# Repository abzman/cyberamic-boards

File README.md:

defunct repo, contents moved to https://github.com/palazzol/CyberamicControlCenter

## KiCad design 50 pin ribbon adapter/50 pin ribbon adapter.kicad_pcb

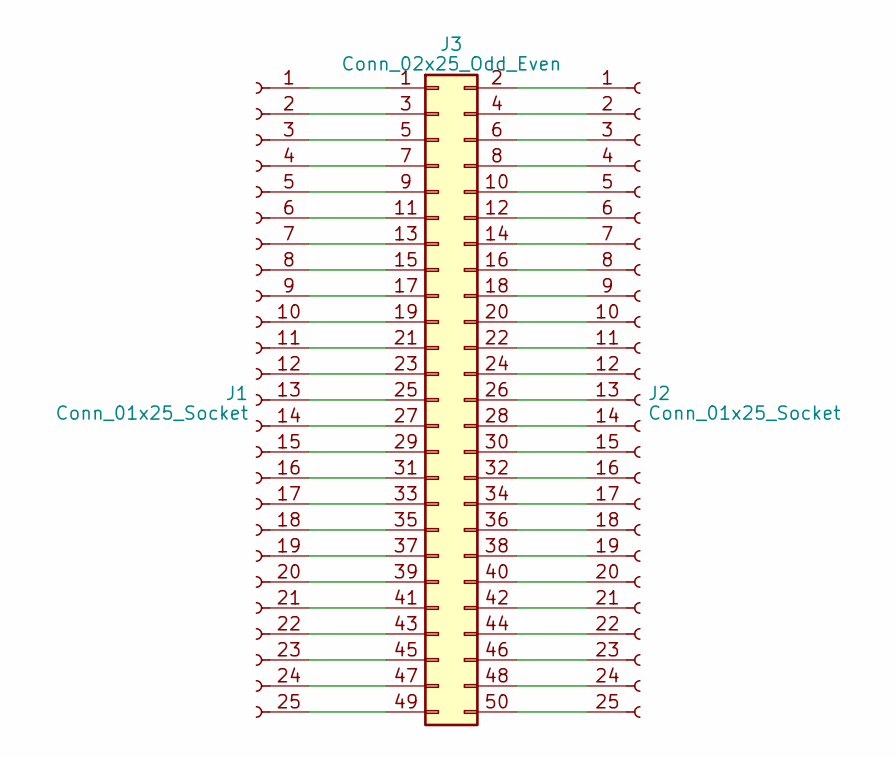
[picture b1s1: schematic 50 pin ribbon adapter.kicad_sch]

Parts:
J1, J2: Conn_01x25_Socket
J3: Conn_02x25_Odd_Even

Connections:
unnamed: J1.1, J3.1
unnamed: J1.2, J3.3
unnamed: J1.3, J3.5
unnamed: J1.4, J3.7
unnamed: J1.5, J3.9
unnamed: J1.6, J3.11
unnamed: J1.7, J3.13
unnamed: J1.8, J3.15
unnamed: J1.9, J3.17
unnamed: J1.10, J3.19
unnamed: J1.11, J3.21
unnamed: J1.12, J3.23
unnamed: J1.13, J3.25
unnamed: J1.14, J3.27
unnamed: J1.15, J3.29
unnamed: J1.16, J3.31
unnamed: J1.17, J3.33
unnamed: J1.18, J3.35
unnamed: J1.19, J3.37
unnamed: J1.20, J3.39
unnamed: J1.21, J3.41
unnamed: J1.22, J3.43
unnamed: J1.23, J3.45
unnamed: J1.24, J3.47
unnamed: J1.25, J3.49
unnamed: J2.1, J3.2
unnamed: J2.2, J3.4
unnamed: J2.3, J3.6
unnamed: J2.4, J3.8
unnamed: J2.5, J3.10
unnamed: J2.6, J3.12
unnamed: J2.7, J3.14
unnamed: J2.8, J3.16
unnamed: J2.9, J3.18
unnamed: J2.10, J3.20
unnamed: J2.11, J3.22
unnamed: J2.12, J3.24
unnamed: J2.13, J3.26
unnamed: J2.14, J3.28
unnamed: J2.15, J3.30
unnamed: J2.16, J3.32
unnamed: J2.17, J3.34
unnamed: J2.18, J3.36
unnamed: J2.19, J3.38
unnamed: J2.20, J3.40
unnamed: J2.21, J3.42
unnamed: J2.22, J3.44
unnamed: J2.23, J3.46
unnamed: J2.24, J3.48
unnamed: J2.25, J3.50

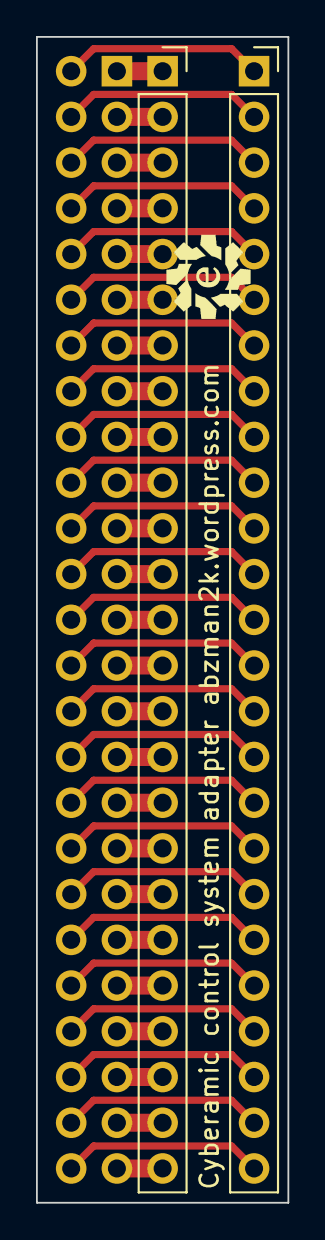
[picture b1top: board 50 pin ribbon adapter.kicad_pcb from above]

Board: 2 copper layers, 14.0 x 64.8 mm, 3 parts (1 on the bottom side), 50 nets.

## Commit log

2023-12-27 first design for adapter, no keying, nothing specific to orientation
2023-12-28 subtle update
2024-01-18 added gerber and image
2024-04-02 fixed silk
2024-05-05 removed board, moved to other repo
